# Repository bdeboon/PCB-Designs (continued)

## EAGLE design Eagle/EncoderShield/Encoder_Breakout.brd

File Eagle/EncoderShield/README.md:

## Arduino Mega Shield 

### Features
- Up to six quadrature encoders
- Up to six 8-bit PWM outputs
- Four I2C ports
- Four SPI ports
- Two bi-directional driver outputs with enabling

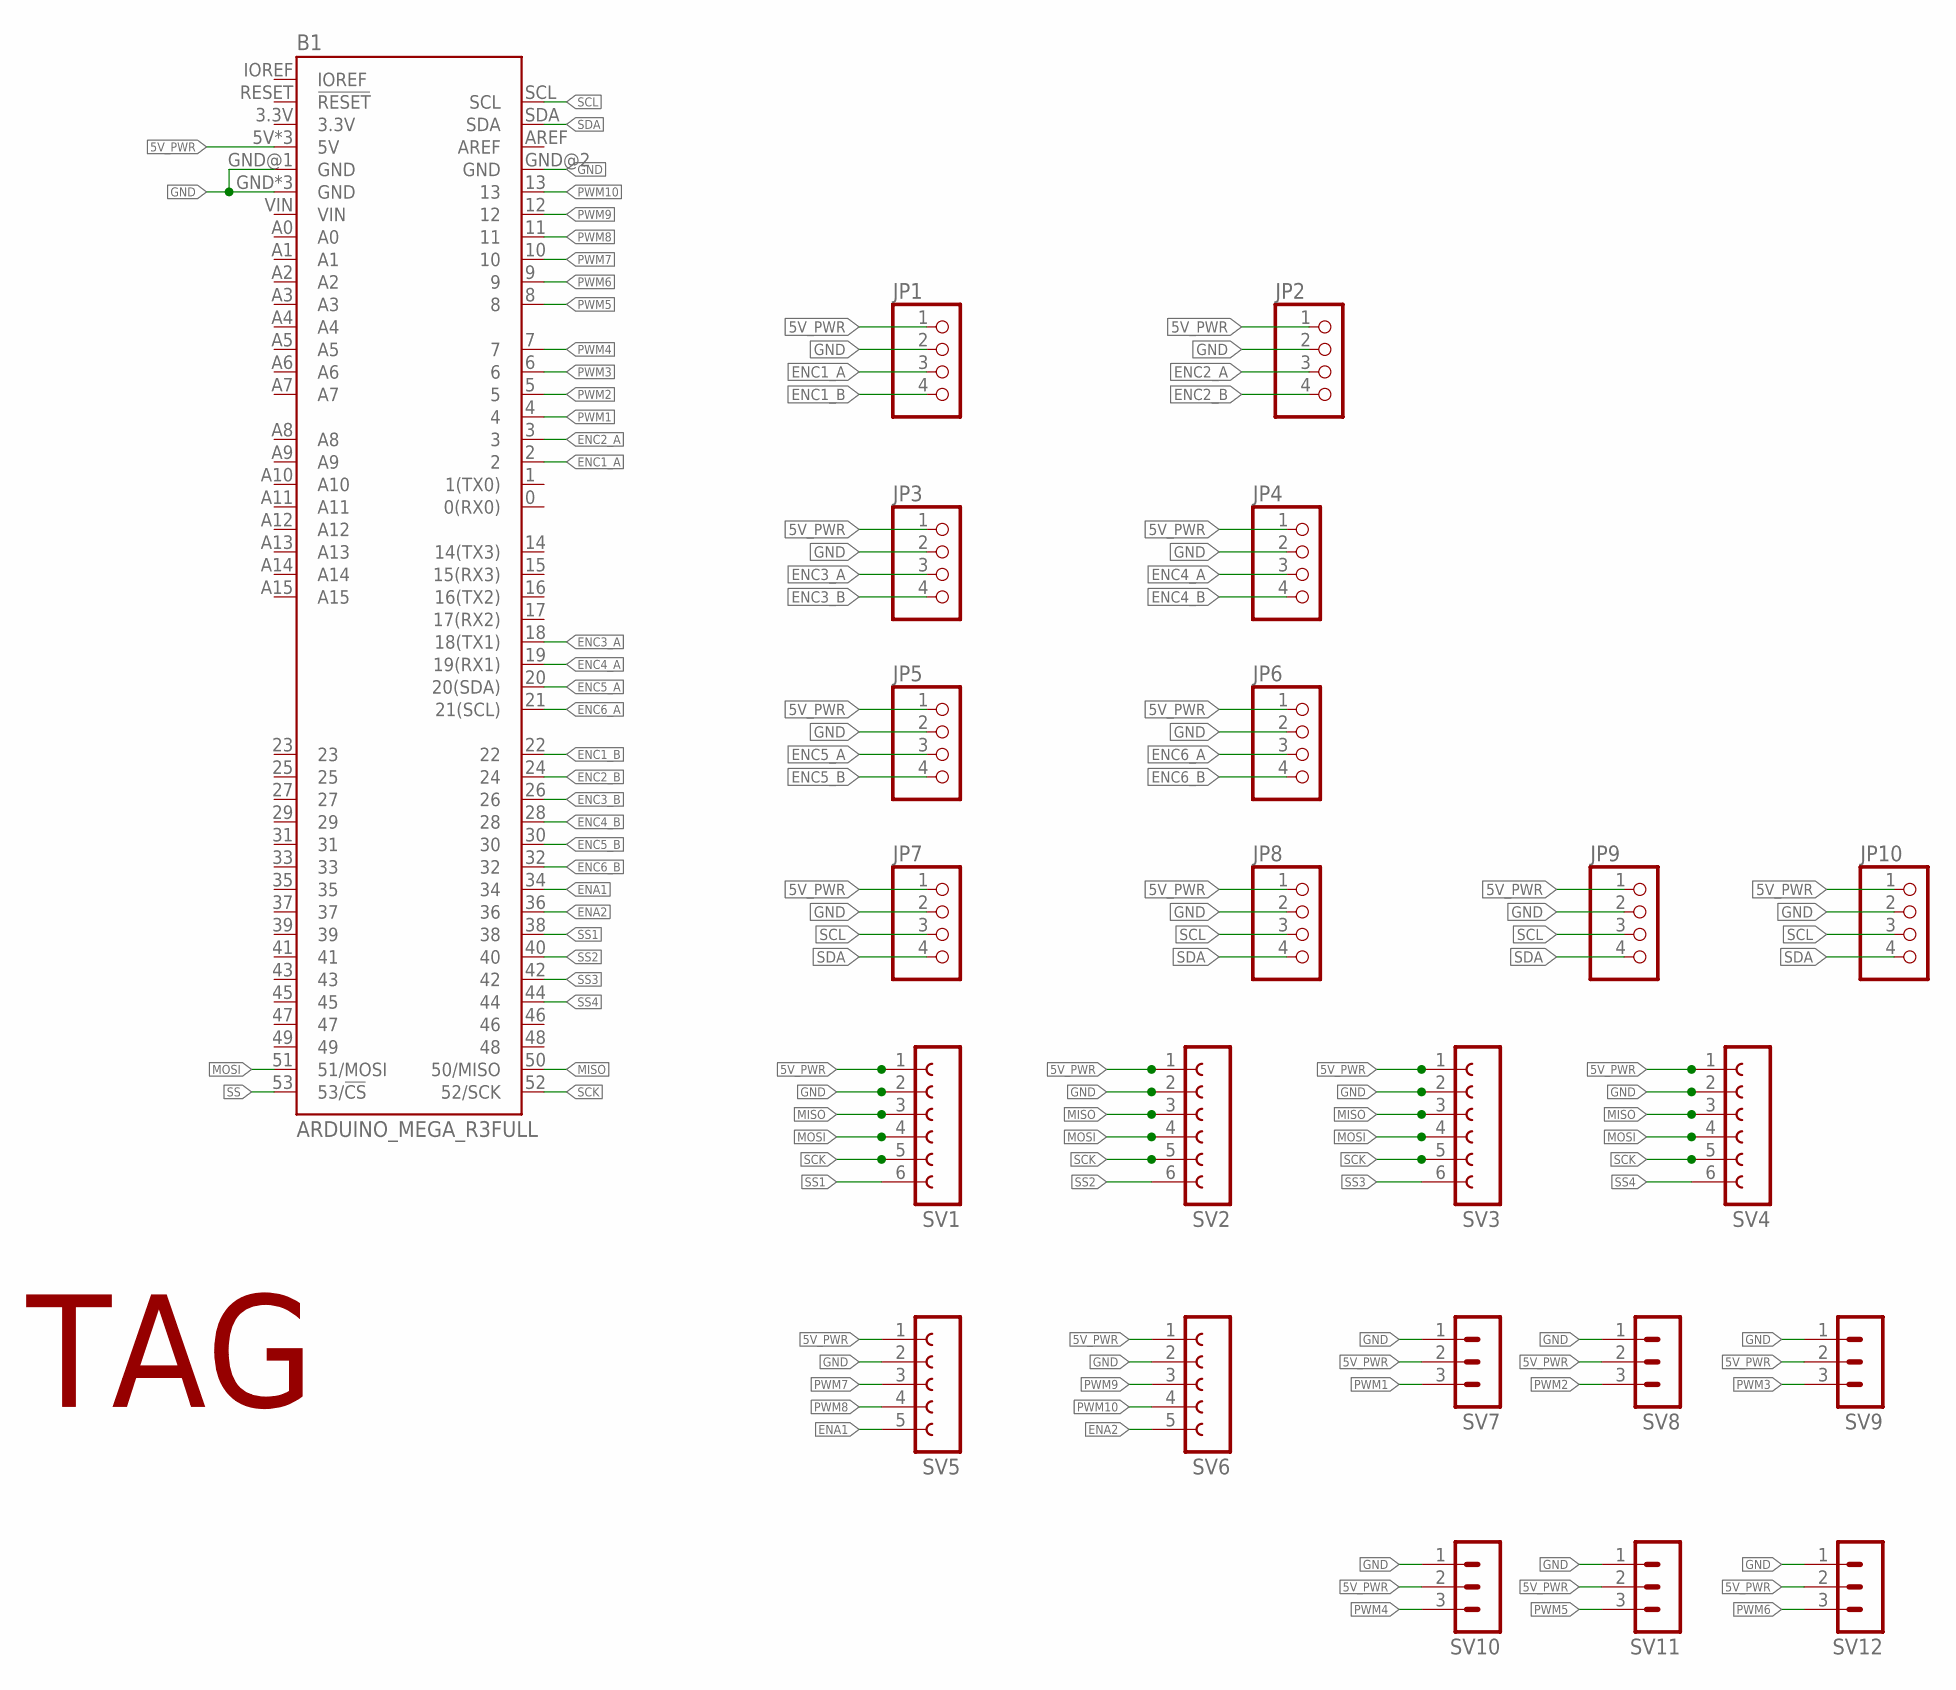
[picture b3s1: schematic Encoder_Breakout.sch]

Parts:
B1: ARDUINO_MEGA_R3FULL; ARDUINO_MEGA_NO_SILK
JP1, JP2, JP3, JP4, JP5, JP6, JP7, JP8, JP9, JP10: PINHD-1X4; 1X04
SV1, SV2, SV3, SV4: FE06-1; FE06
SV5, SV6: FE05-1
SV7, SV8, SV9, SV10, SV11, SV12: MA03-1
U$1: TAG

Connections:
5V_PWR: B1.5V, B1.5V@1 (5V), B1.5V@2 (5V), JP1.1, JP2.1, JP3.1, JP4.1, JP5.1, JP6.1, JP7.1, JP8.1, JP9.1, JP10.1, SV1.1, SV2.1, SV3.1, SV4.1, SV5.1, SV6.1, SV7.2, SV8.2, SV9.2, SV10.2, SV11.2, SV12.2
ENA1: B1.34, SV5.5
ENA2: B1.36, SV6.5
ENC1_A: B1.2, JP1.3
ENC1_B: B1.22, JP1.4
ENC2_A: B1.3, JP2.3
ENC2_B: B1.24, JP2.4
ENC3_A: B1.18 (18(TX1)), JP3.3
ENC3_B: B1.26, JP3.4
ENC4_A: B1.19 (19(RX1)), JP4.3
ENC4_B: B1.28, JP4.4
ENC5_A: B1.20 (20(SDA)), JP5.3
ENC5_B: B1.30, JP5.4
ENC6_A: B1.21 (21(SCL)), JP6.3
ENC6_B: B1.32, JP6.4
GND: B1.GND, B1.GND@1 (GND), B1.GND@2 (GND), B1.GND@3 (GND), B1.GND@4 (GND), JP1.2, JP2.2, JP3.2, JP4.2, JP5.2, JP6.2, JP7.2, JP8.2, JP9.2, JP10.2, SV1.2, SV2.2, SV3.2, SV4.2, SV5.2, SV6.2, SV7.1, SV8.1, SV9.1, SV10.1, SV11.1, SV12.1
MISO: B1.50 (50/MISO), SV1.3, SV2.3, SV3.3, SV4.3
MOSI: B1.51 (51/MOSI), SV1.4, SV2.4, SV3.4, SV4.4
PWM1: B1.4, SV7.3
PWM2: B1.5, SV8.3
PWM3: B1.6, SV9.3
PWM4: B1.7, SV10.3
PWM5: B1.8, SV11.3
PWM6: B1.9, SV12.3
PWM7: B1.10, SV5.3
PWM8: B1.11, SV5.4
PWM9: B1.12, SV6.3
PWM10: B1.13, SV6.4
SCK: B1.52 (52/SCK), SV1.5, SV2.5, SV3.5, SV4.5
SCL: B1.SCL, JP7.3, JP8.3, JP9.3, JP10.3
SDA: B1.SDA, JP7.4, JP8.4, JP9.4, JP10.4
SS: B1.53 (53/!CS)
SS1: B1.38, SV1.6
SS2: B1.40, SV2.6
SS3: B1.42, SV3.6
SS4: B1.44, SV4.6

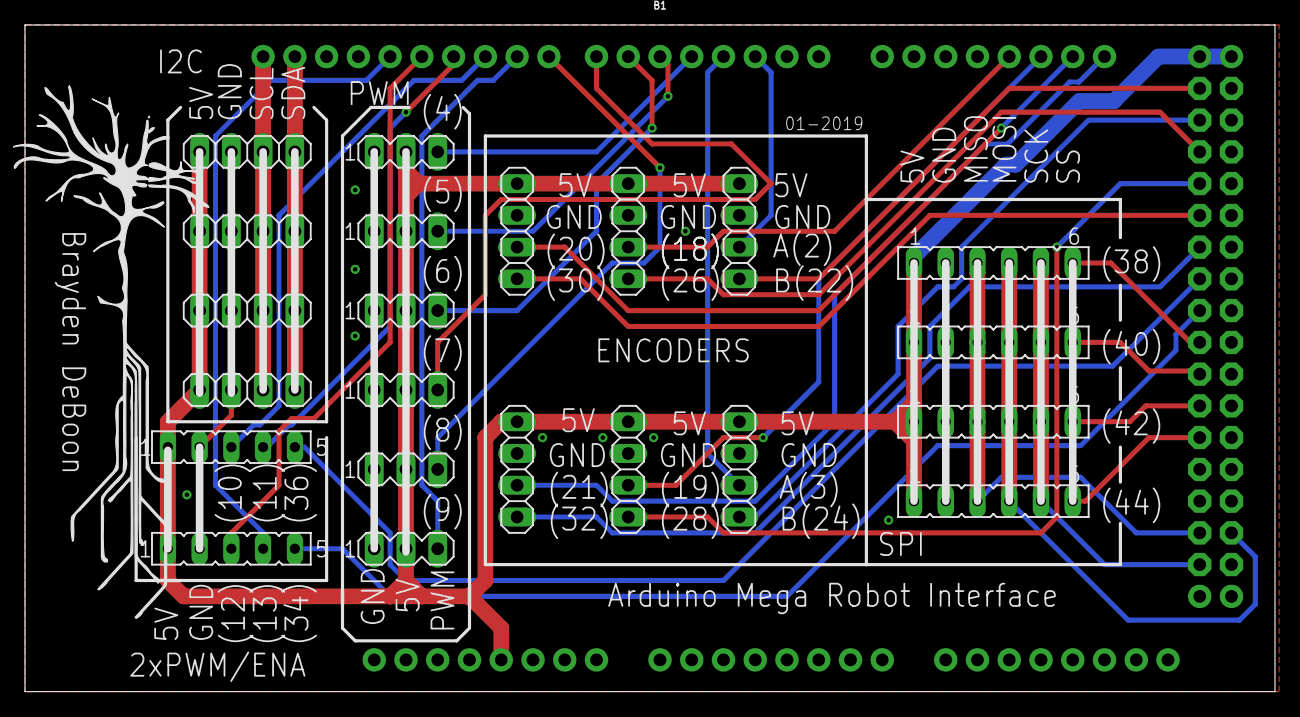
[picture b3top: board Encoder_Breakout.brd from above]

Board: 2 copper layers, 100.0 x 53.3 mm, 24 parts (0 on the bottom side), 35 nets.

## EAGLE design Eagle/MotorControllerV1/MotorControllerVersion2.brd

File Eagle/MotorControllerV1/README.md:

Eagle Files for ethernet-interfaced motor controller

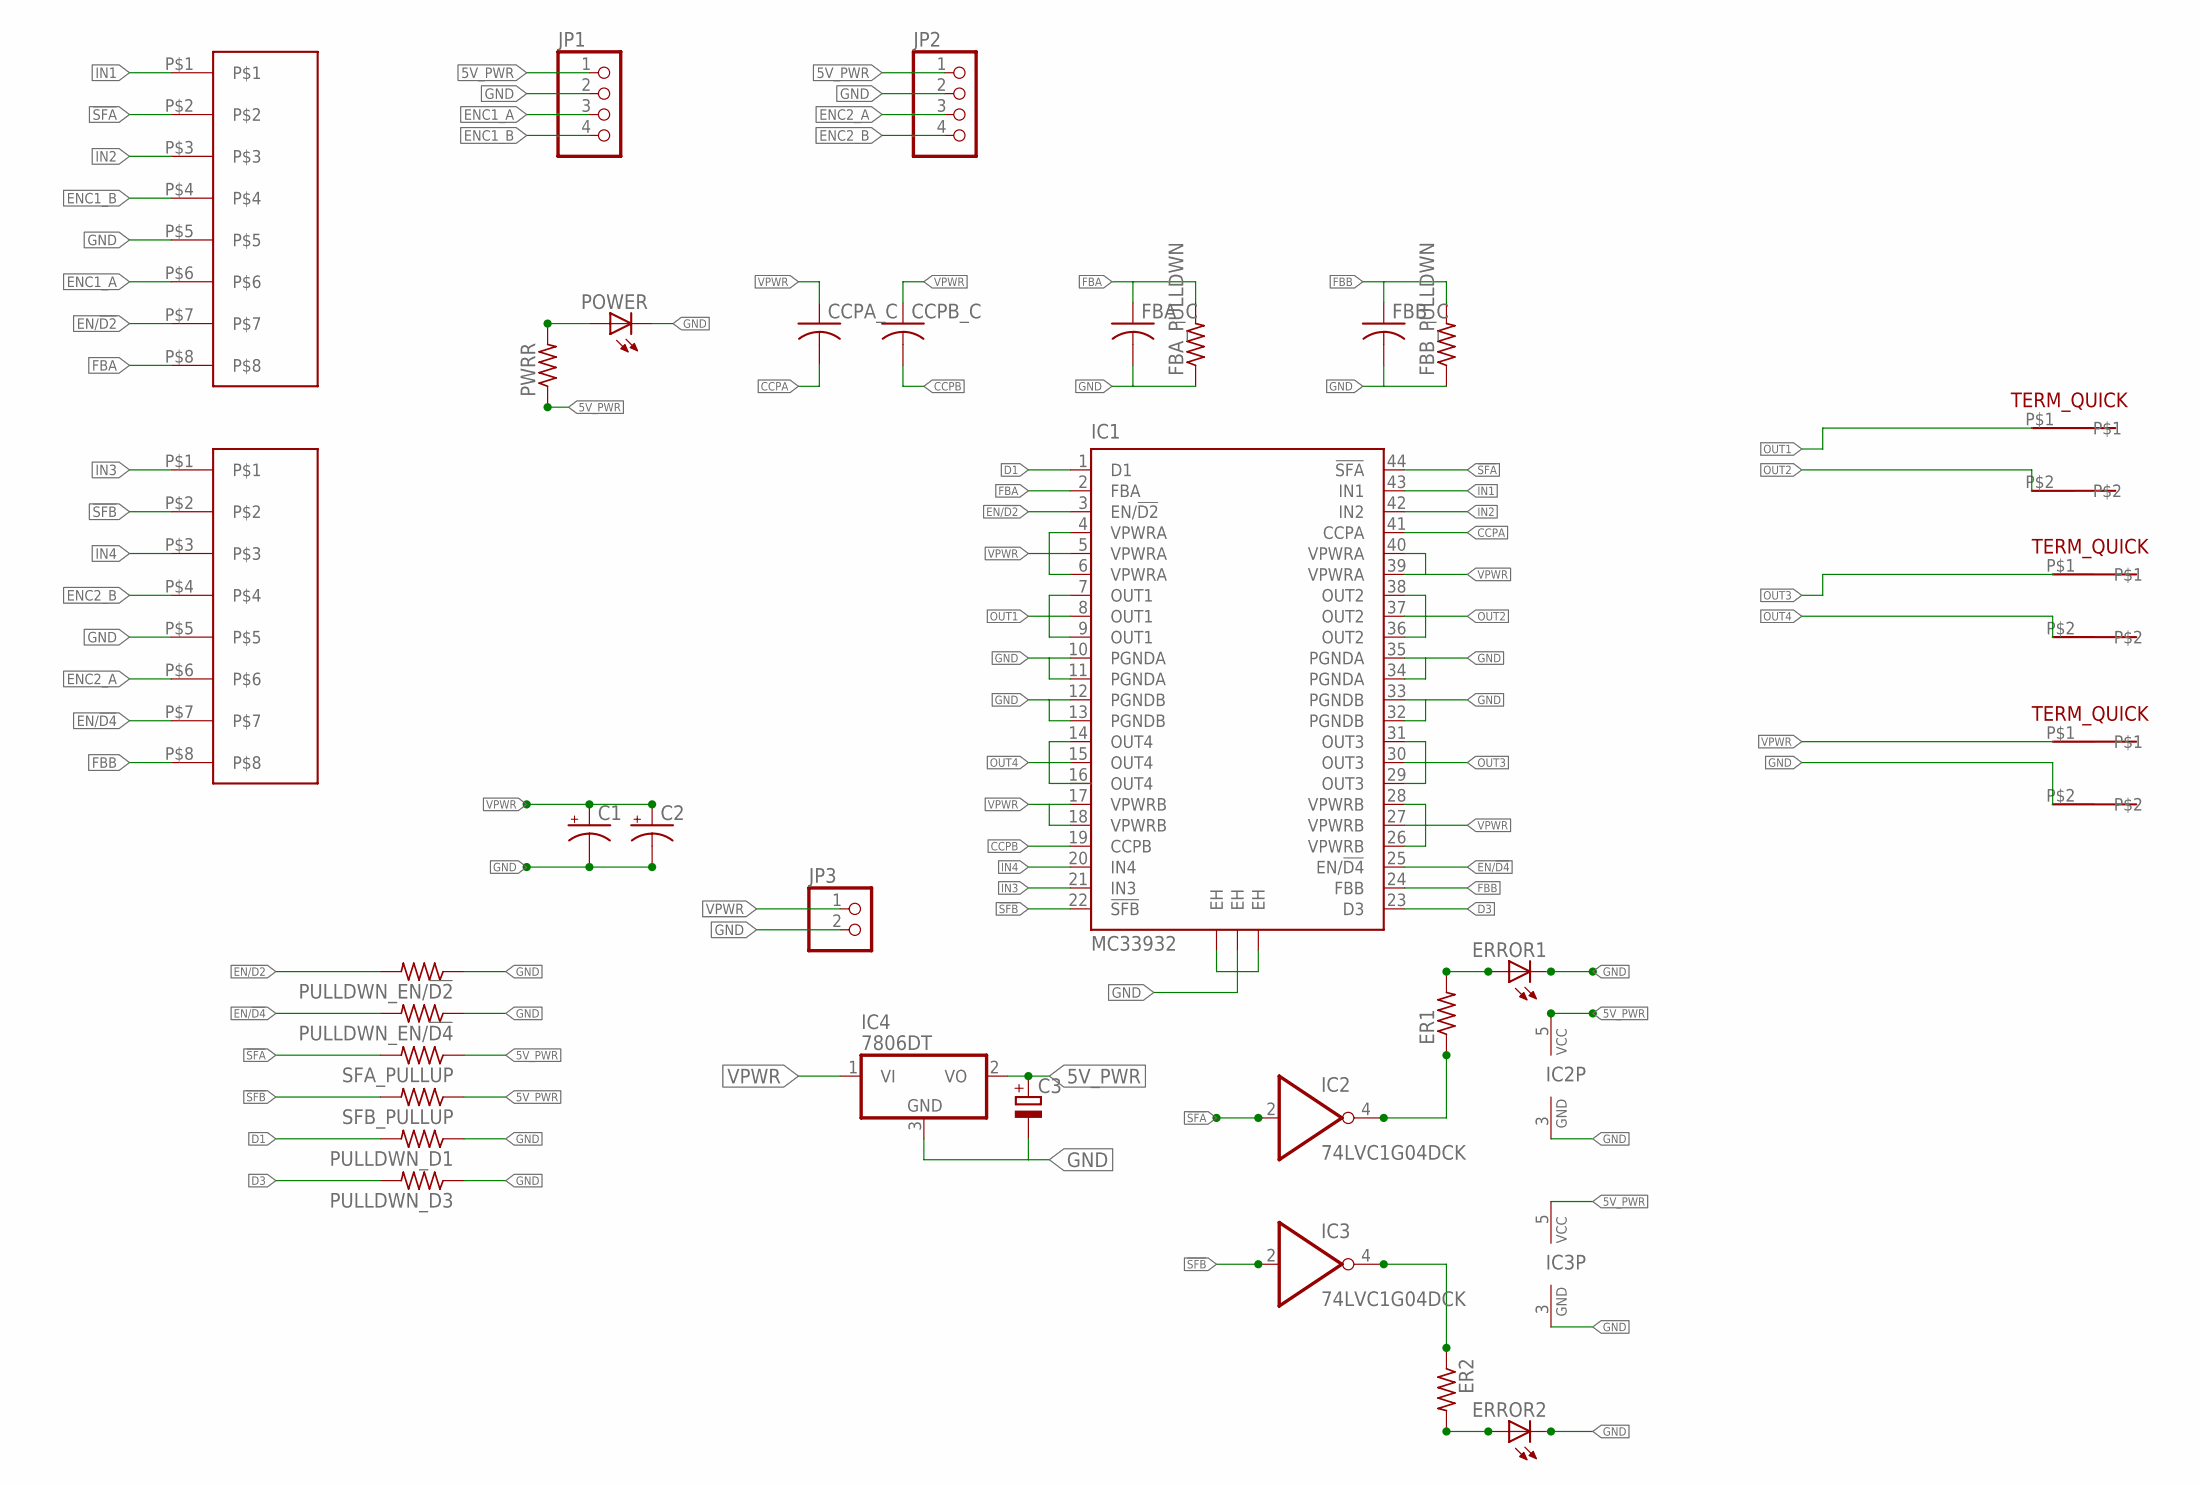
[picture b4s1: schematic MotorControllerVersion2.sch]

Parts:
C1, C2: CPOL-US153CLV-0810; 153CLV-0810
C3: CPOL-EU153CLV-0405; 153CLV-0405
CCPA_C: C-USC0805; C0805
CCPB_C: C-USC0805; C0805
ER1, ER2: R-US_R0805; R0805
ERROR1, ERROR2: LED_E; LED_1206
FBA_C: C-USC0805; C0805
FBA_PULLDWN: R-US_R0805; R0805
FBB_C: C-USC0805; C0805
FBB_PULLDWN: R-US_R0805; R0805
IC1: MC33932; HSOP44
IC2, IC3: 74LVC1G04DCK; SC70-5
IC4: 7806DT; TO252
JP1, JP2: PINHD-1X4; 1X04
JP3: PINHD-1X2; 1X02
POWER: LED_E; LED_1206
PULLDWN_D1, PULLDWN_D3: R-US_R0805; R0805
PULLDWN_EN/!D2, PULLDWN_EN/!D4: R-US_R0805; R0805
PWRR: R-US_R0805; R0805
SFA_PULLUP: R-US_R0805; R0805
SFB_PULLUP: R-US_R0805; R0805
U$1, U$2: ETHERNETPORT
U$3, U$4, U$5: TERM_QUICK

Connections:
5V_PWR: C3.+, IC2.5 (VCC), IC3.5 (VCC), IC4.2 (VO), JP1.1, JP2.1, PWRR.1, SFA_PULLUP.1, SFB_PULLUP.1
!SFA: IC1.44 (!SFA), IC2.2 (I), SFA_PULLUP.2, U$1.P$2
!SFB: IC1.22 (!SFB), IC3.2 (I), SFB_PULLUP.2, U$2.P$2
CCPA: CCPA_C.2, IC1.41 (CCPA)
CCPB: CCPB_C.2, IC1.19 (CCPB)
D1: IC1.1 (D1), PULLDWN_D1.2
D3: IC1.23 (D3), PULLDWN_D3.2
EN/!D2: IC1.3 (EN/!D2), PULLDWN_EN/!D2.2, U$1.P$7
EN/!D4: IC1.25 (EN/!D4), PULLDWN_EN/!D4.2, U$2.P$7
ENC1_A: JP1.3, U$1.P$6
ENC1_B: JP1.4, U$1.P$4
ENC2_A: JP2.3, U$2.P$6
ENC2_B: JP2.4, U$2.P$4
FBA: FBA_C.1, FBA_PULLDWN.2, IC1.2 (FBA), U$1.P$8
FBB: FBB_C.1, FBB_PULLDWN.2, IC1.24 (FBB), U$2.P$8
GND: C1.-, C2.-, C3.-, ERROR1.C, ERROR2.C, FBA_C.2, FBA_PULLDWN.1, FBB_C.2, FBB_PULLDWN.1, IC1.10 (PGNDA), IC1.11 (PGNDA), IC1.12 (PGNDB), IC1.13 (PGNDB), IC1.32 (PGNDB), IC1.33 (PGNDB), IC1.34 (PGNDA), IC1.35 (PGNDA), IC1.EH@1 (EH), IC1.EH@2 (EH), IC1.EH@3 (EH), IC2.3 (GND), IC3.3 (GND), IC4.3 (GND), JP1.2, JP2.2, JP3.2, POWER.C, PULLDWN_D1.1, PULLDWN_D3.1, PULLDWN_EN/!D2.1, PULLDWN_EN/!D4.1, U$1.P$5, U$2.P$5, U$5.P$2
IN1: IC1.43 (IN1), U$1.P$1
IN2: IC1.42 (IN2), U$1.P$3
IN3: IC1.21 (IN3), U$2.P$1
IN4: IC1.20 (IN4), U$2.P$3
unnamed: ER2.1, IC3.4 (O)
unnamed: POWER.A, PWRR.2
unnamed: ER1.1, IC2.4 (O)
unnamed: ER1.2, ERROR1.A
unnamed: ER2.2, ERROR2.A
OUT1: IC1.7 (OUT1), IC1.8 (OUT1), IC1.9 (OUT1), U$3.P$1
OUT2: IC1.36 (OUT2), IC1.37 (OUT2), IC1.38 (OUT2), U$3.P$2
OUT3: IC1.29 (OUT3), IC1.30 (OUT3), IC1.31 (OUT3), U$4.P$1
OUT4: IC1.14 (OUT4), IC1.15 (OUT4), IC1.16 (OUT4), U$4.P$2
VPWR: C1.+, C2.+, CCPA_C.1, CCPB_C.1, IC1.4 (VPWRA), IC1.5 (VPWRA), IC1.6 (VPWRA), IC1.17 (VPWRB), IC1.18 (VPWRB), IC1.26 (VPWRB), IC1.27 (VPWRB), IC1.28 (VPWRB), IC1.39 (VPWRA), IC1.40 (VPWRA), IC4.1 (VI), JP3.1, U$5.P$1

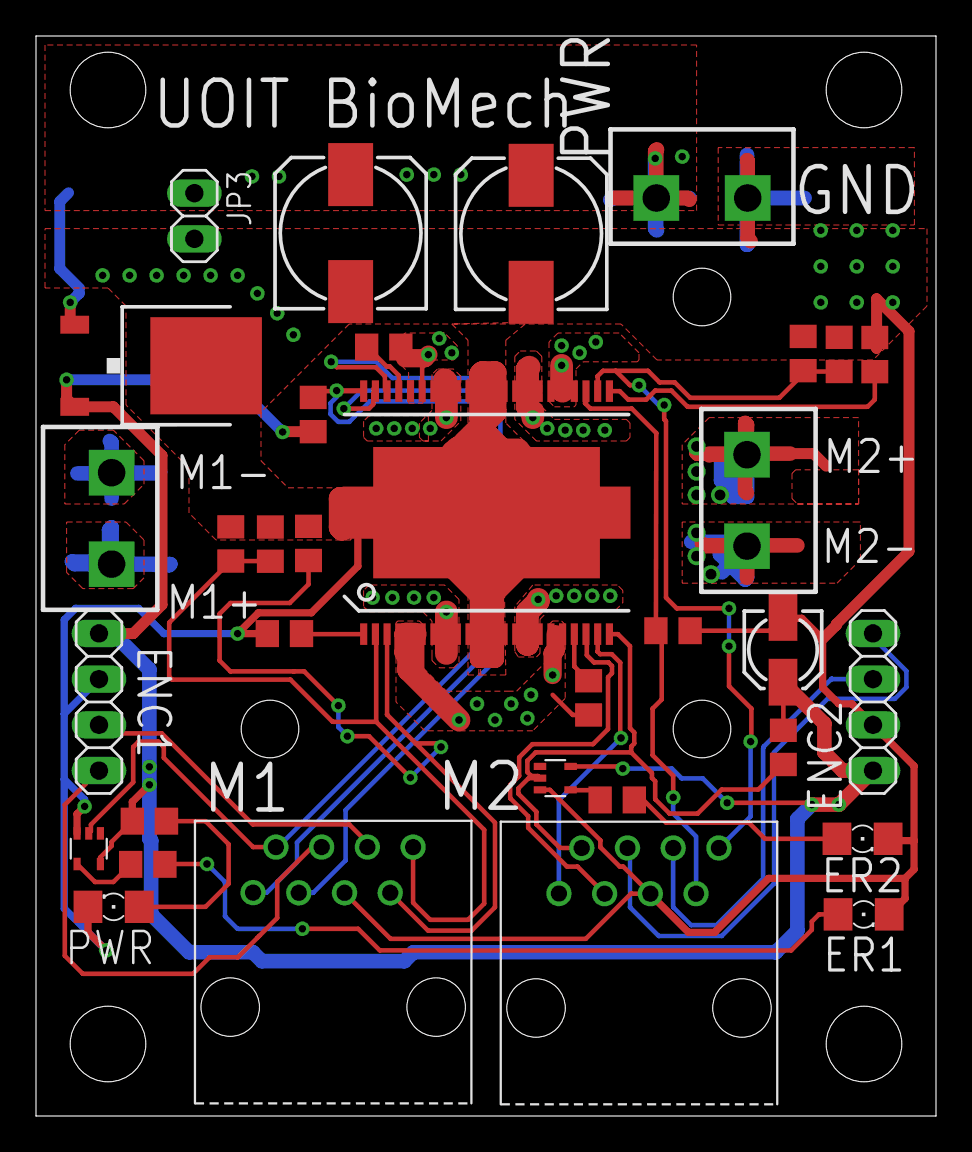
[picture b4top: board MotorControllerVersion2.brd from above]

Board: 2 copper layers, 50.0 x 60.0 mm, 33 parts (0 on the bottom side), 30 nets.

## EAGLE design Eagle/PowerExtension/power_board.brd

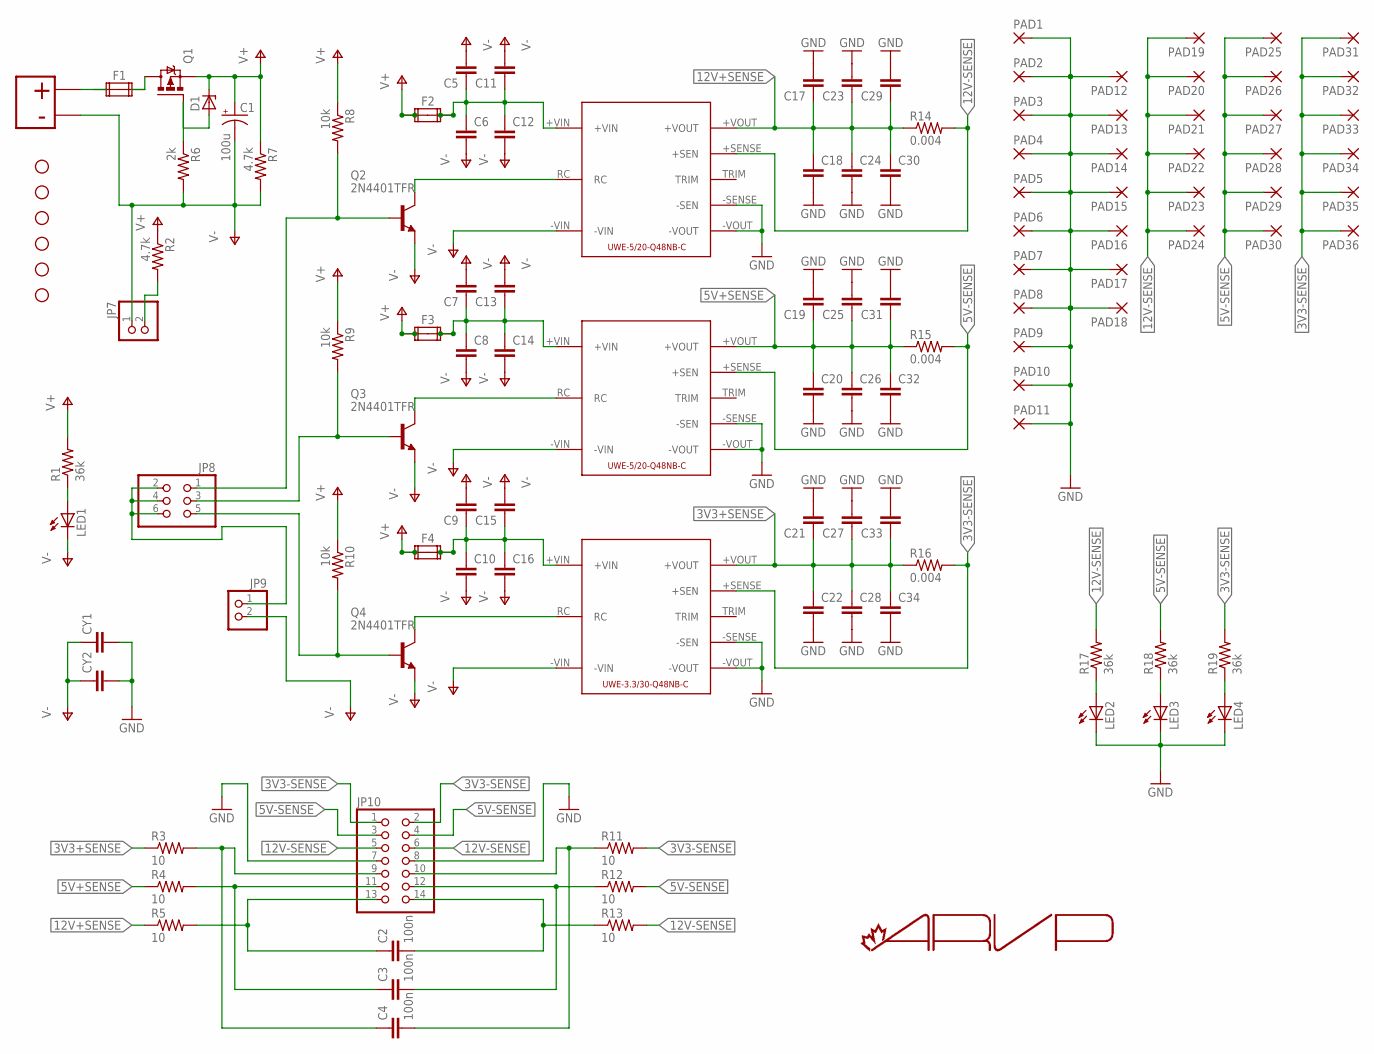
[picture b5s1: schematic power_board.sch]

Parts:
C1: 100u; E3,5-8
C2, C3, C4: 100n; C025-024X044
C5, C6, C7, C8, C9, C10, C11, C12, C13, C14, C15, C16: C-EU050-035X075; C050-035X075
C17, C18, C19, C20, C21, C22, C23, C24, C25, C26, C27, C28, C29, C30, C31, C32, C33, C34: C-EU025-040X050; C025-040X050
CY1, CY2: CYYC7B5; YC7B5
D1: BZV10; DO34Z7
F1, F2, F3, F4: FUSE2P; FUSE1
JP1, JP2, JP3, JP4, JP5, JP6: STAND-OFF
JP7, JP9: PINHD-1X2/90; 1X02/90
JP8: PINHD-2X3/90; 2X03/90
JP10: PINHD-2X7; 2X07
LED1, LED2, LED3, LED4: LED3MM
PAD1, PAD2, PAD3, PAD4, PAD5, PAD6, PAD7, PAD8, PAD9, PAD10, PAD11, PAD12, PAD13, PAD14, PAD15, PAD16, PAD17, PAD18, PAD19, PAD20, PAD21, PAD22, PAD23, PAD24, PAD25, PAD26, PAD27, PAD28, PAD29, PAD30, PAD31, PAD32, PAD33, PAD34, PAD35, PAD36: WIREPAD3,17/1,3; 3,17/1,3
Q1: IPP80P03P4L04AKSA1; TO220BV
Q2, Q3, Q4: 2N4401TFR; TO92-EBC
R1, R17, R18, R19: 36k; 0204/7
R2, R7: 4.7k; 0204/7
R3, R4, R5, R11, R12, R13: 10; 0204/5
R6: 2k; 0204/7
R8, R9, R10: 10k; 0204/7
R14, R15, R16: 0.004; 0617/22
T1: 2_POS_TERMINAL; PHOENIX_CONTACT_MKDS_5/2-7.62
U1: UWE-5/20-Q48NB-C; UWE-100-120W
U2: UWE-3.3/30-Q48NB-C; UWE-100-120W
U4: UWE-12/10-Q48NB-C; UWE-100-120W

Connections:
3V3+SENSE: C21.1, C22.1, C27.1, C28.1, C33.1, C34.1, R3.1, R16.1, U2.+VOUT
3V3-SENSE: JP10.1, JP10.2, PAD31.1, PAD32.1, PAD33.1, PAD34.1, PAD35.1, PAD36.1, R11.2, R16.2, R19.2, U2.+SENSE (+SEN)
5V+SENSE: C19.1, C20.1, C25.1, C26.1, C31.1, C32.1, R4.1, R15.1, U1.+VOUT
5V-SENSE: JP10.3, JP10.4, PAD25.1, PAD26.1, PAD27.1, PAD28.1, PAD29.1, PAD30.1, R12.2, R15.2, R18.2, U1.+SENSE (+SEN)
12V+SENSE: C17.1, C18.1, C23.1, C24.1, C29.1, C30.1, R5.1, R14.1, U4.+VOUT
12V-SENSE: JP10.5, JP10.6, PAD19.1, PAD20.1, PAD21.1, PAD22.1, PAD23.1, PAD24.1, R13.2, R14.2, R17.2, U4.+SENSE (+SEN)
ENABLE_3V3: Q4.C, U2.RC
ENABLE_5V: Q3.C, U1.RC
ENABLE_12V: Q2.C, U4.RC
GND: C17.2, C18.2, C19.2, C20.2, C21.2, C22.2, C23.2, C24.2, C25.2, C26.2, C27.2, C28.2, C29.2, C30.2, C31.2, C32.2, C33.2, C34.2, CY1.2, CY2.2, JP10.7, JP10.8, LED2.K (C), LED3.K (C), LED4.K (C), PAD1.1, PAD2.1, PAD3.1, PAD4.1, PAD5.1, PAD6.1, PAD7.1, PAD8.1, PAD9.1, PAD10.1, PAD11.1, PAD12.1, PAD13.1, PAD14.1, PAD15.1, PAD16.1, PAD17.1, PAD18.1, U1.-SENSE (-SEN), U1.-VOUT, U2.-SENSE (-SEN), U2.-VOUT, U4.-SENSE (-SEN), U4.-VOUT
J3: C4.1, JP10.9, R3.2
J4: C4.2, JP10.10, R11.1
J5: C3.1, JP10.11, R4.2
J6: C3.2, JP10.12, R12.1
J7: C2.1, JP10.13, R5.2
J8: C2.2, JP10.14, R13.1
unnamed: LED1.A, R1.1
unnamed: JP7.2, R2.2
unnamed: F1.1A, F1.1B, T1.P$1
unnamed: D1.A, Q1.G, R6.1
unnamed: C5.1, C6.1, C11.1, C12.1, F2.2A, F2.2B, U4.+VIN
unnamed: C7.1, C8.1, C13.1, C14.1, F3.2A, F3.2B, U1.+VIN
unnamed: JP8.2, JP8.4, JP8.6, JP9.1
unnamed: LED2.A, R17.1
unnamed: LED3.A, R18.1
unnamed: LED4.A, R19.1
unnamed: C9.1, C10.1, C15.1, C16.1, F4.2A, F4.2B, U2.+VIN
ON/OFF_1: JP8.1, Q2.B, R8.2
ON/OFF_2: JP8.3, Q3.B, R9.2
ON/OFF_3: JP8.5, Q4.B, R10.2
V+: C1.+, D1.C, F2.1A, F2.1B, F3.1A, F3.1B, F4.1A, F4.1B, Q1.S, R1.2, R2.1, R7.1, R8.1, R9.1, R10.1
V-: C1.-, C5.2, C6.2, C7.2, C8.2, C9.2, C10.2, C11.2, C12.2, C13.2, C14.2, C15.2, C16.2, CY1.1, CY2.1, JP7.1, JP9.2, LED1.K (C), Q2.E, Q3.E, Q4.E, R6.2, R7.2, T1.P$2, U1.-VIN, U2.-VIN, U4.-VIN
VBAT+: F1.2A, F1.2B, Q1.D

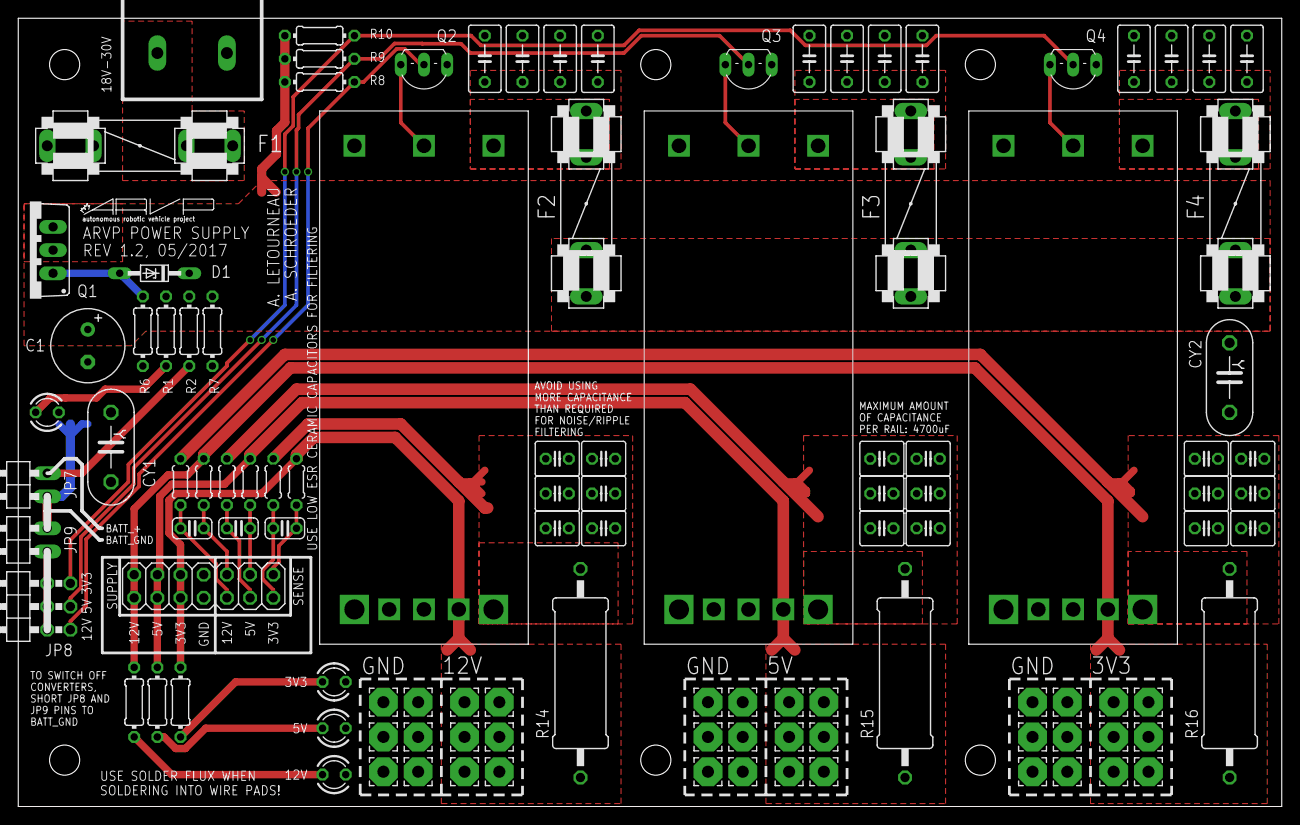
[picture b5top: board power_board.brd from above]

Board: 2 copper layers, 138.4 x 86.4 mm, 121 parts (0 on the bottom side), 33 nets.

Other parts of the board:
U$1: FRAME_A_L
U$2: DOCFIELD
U$3: ARVP

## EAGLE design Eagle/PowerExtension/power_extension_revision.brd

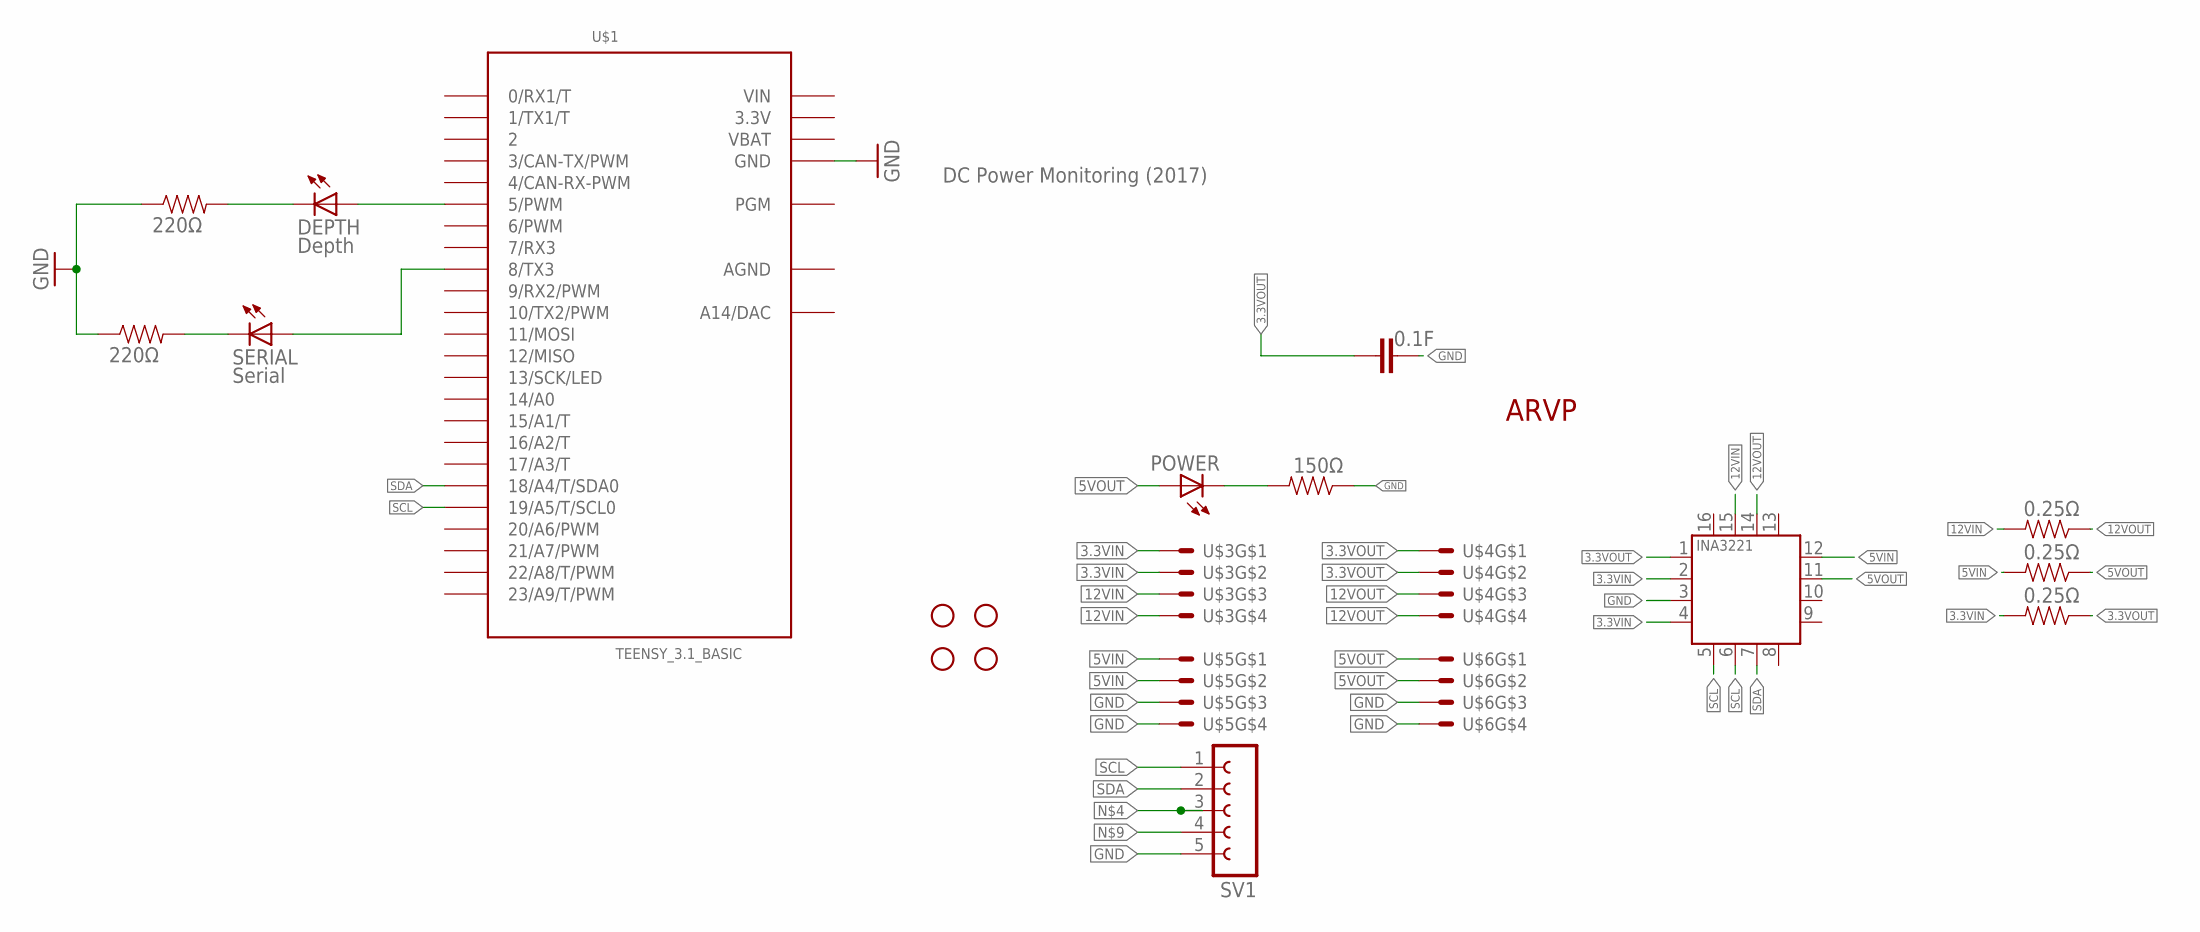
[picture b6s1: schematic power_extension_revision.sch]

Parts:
C1: 0.1F; 0805
DEPTH: Depth; CHIP-LED0805
JP1, JP2, JP3, JP4: STAND-OFF
POWER: LEDCHIP-LED0805; CHIP-LED0805
R1: 150Ω; 0805
R4, R5, R18: 0.25Ω; 0805
R7, R8: 220Ω; 0805
SERIAL: Serial; CHIP-LED0805
SV1: FE05-1
U1: INA3221.; HVQFN16_4X4
U$1: TEENSY_3.1_BASIC
U$2: ARVP_LOGO; ARVP
U$3, U$4, U$5, U$6: MOLEX-44472-0454; 4.2MM_PITCH_HOLESX4

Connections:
3.3V: U$1.3.3V, U$1.3.3V1 (3.3V)
3.3VIN: R5.2, U1.2 (IN+3), U1.4 (VS), U$3.P$1, U$3.P$2
3.3VOUT: C1.1, R5.1, U1.1 (IN-3), U$4.P$1, U$4.P$2
5VIN: R4.2, U1.12 (IN+1), U$5.P$1, U$5.P$2
5VOUT: POWER.A, R4.1, U1.11 (IN-1), U$6.P$1, U$6.P$2
12VIN: R18.2, U1.15 (IN+2), U$3.P$3, U$3.P$4
12VOUT: R18.1, U1.14 (IN-2), U$4.P$3, U$4.P$4
AGND: U$1.AGND
GND: C1.2, R1.1, R7.1, R8.1, SV1.5, U1.3 (GND), U$1.GND, U$1.GND1 (GND), U$5.P$3, U$5.P$4, U$6.P$3, U$6.P$4
unnamed: POWER.C, R1.2
unnamed: DEPTH.A, SV1.3, U$1.5 (5/PWM)
unnamed: R7.2, SERIAL.C
unnamed: SERIAL.A, SV1.4, U$1.8 (8/TX3)
unnamed: DEPTH.C, R8.2
SCL: SV1.1, U1.5 (A0), U1.6 (SCL), U$1.19/A5 (19/A5/T/SCL0)
SDA: SV1.2, U1.7 (SDA), U$1.18/A4 (18/A4/T/SDA0)
VBAT: U$1.VBAT
VIN: U$1.VIN

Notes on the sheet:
DC Power Monitoring (2017)

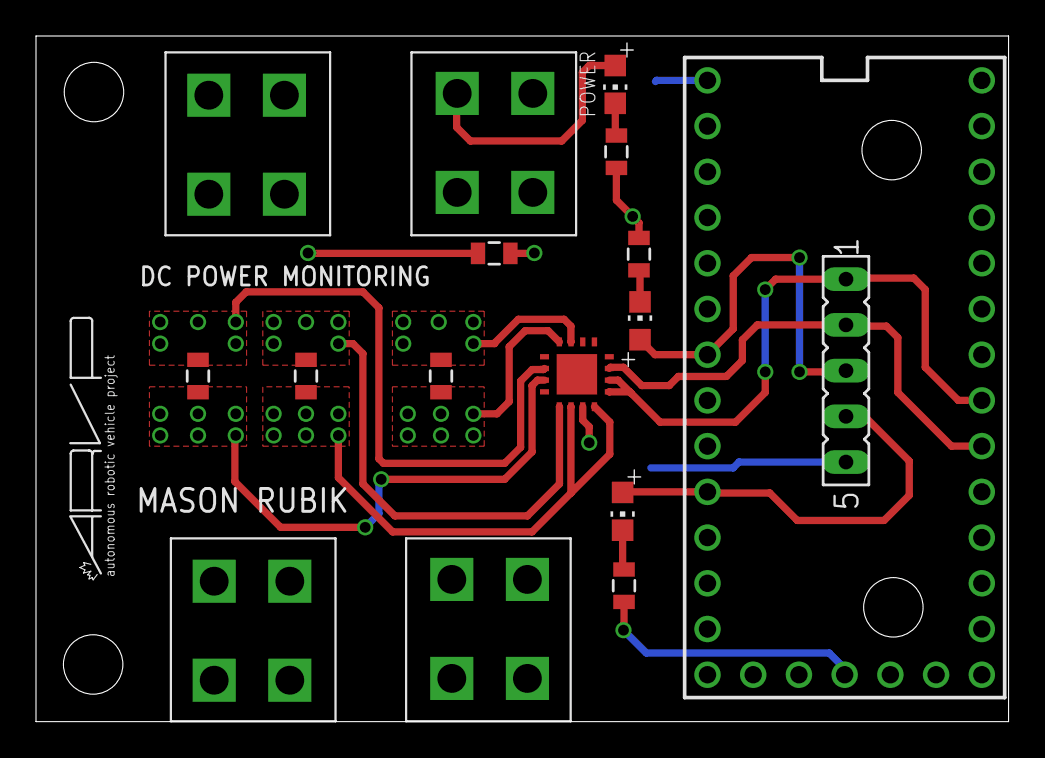
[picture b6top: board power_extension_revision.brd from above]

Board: 2 copper layers, 54.0 x 38.1 mm, 22 parts (0 on the bottom side), 15 nets.
